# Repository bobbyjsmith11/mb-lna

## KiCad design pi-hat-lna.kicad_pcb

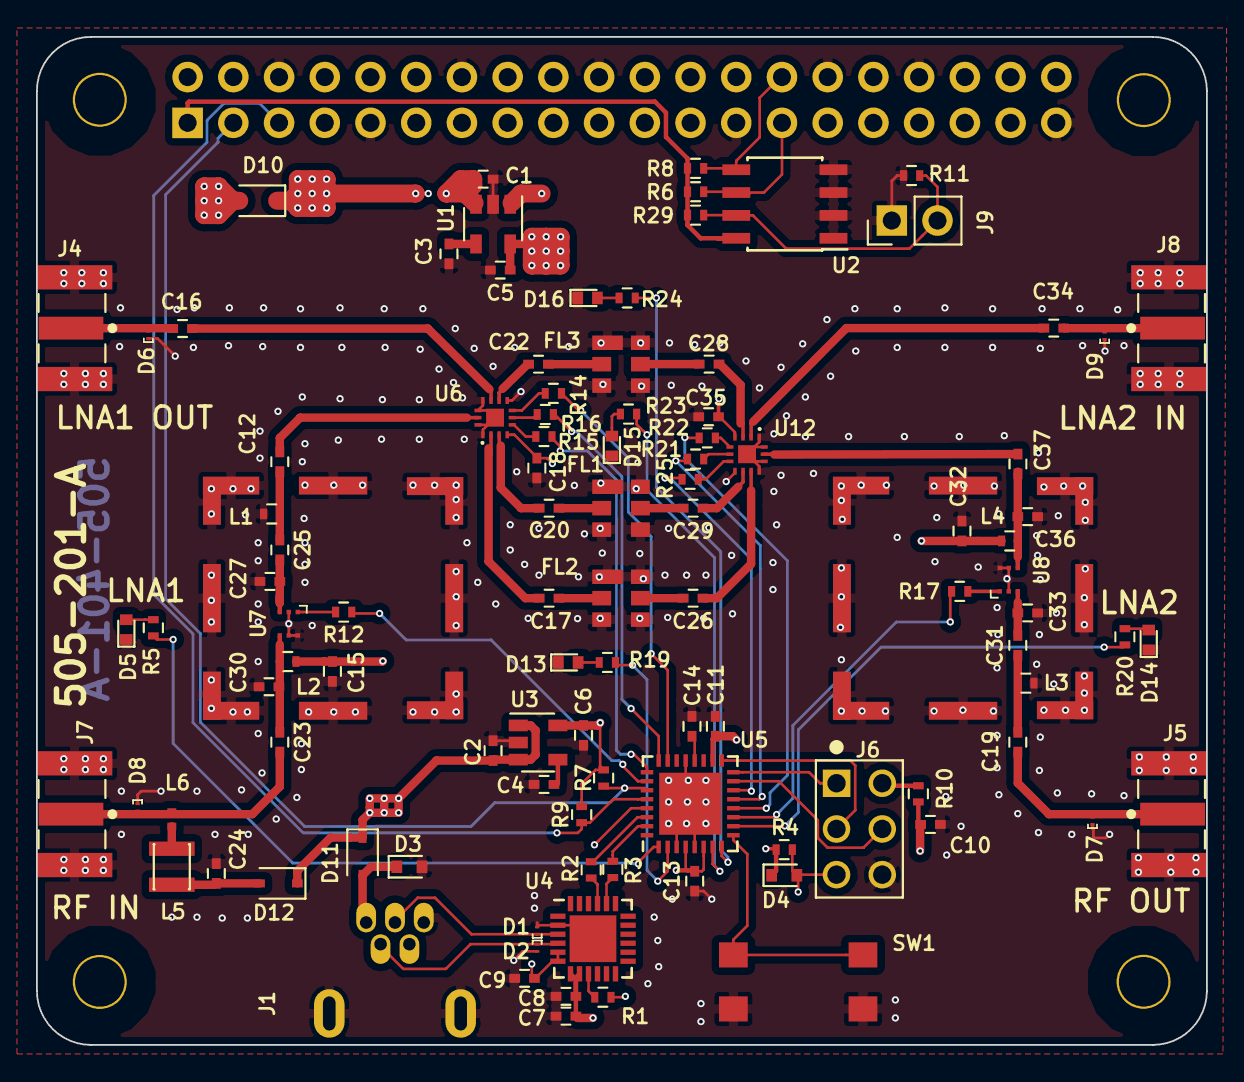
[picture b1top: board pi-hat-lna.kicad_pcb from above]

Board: 4 copper layers, 65.0 x 56.0 mm, 109 parts (1 on the bottom side), 83 nets.

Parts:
C1, C2, C5, C6, C7, C24: 1uF; C_0402
C3, C4, C8, C10, C11, C13, C14, C15, C18, C32, C35: 100nF; C_0402
C9: 4.7uF; C_0402
C12, C16, C17, C19, C20, C22, C23, C26, C28, C29, C34, C37: 100pF; C_0402
C25, C31: 30pF; C_0402
C27, C33: DNF; C_0402
C30, C36: 1pF; C_0402
D1, D2, D6, D7, D8, D9: ESD8472MUT5G; ONSEMI_0201_DSN2_153AF
D3, D4: PESD12VS1UB,115; D_SOD-523
D5, D13, D14, D15, D16: SML-LX0402SUGC-TR; LED_0402
D10, D11, D12: BAT165; D_SOD-323
FL1: SF2098E; SAW_3X3mm
FL2: SF2250E; SAW_3X3mm
FL3: SF2275E; SAW_3X3mm
H1, H2, H3, H4: 3mm_Mounting_Hole; NPTH_3mm_ID
J1: USB_B_Mini; USB_Mini-B_Molex-054819-0519
J3: DNF; PinSocket_2x20_P2.54mm_Vertical
J4, J5, J7, J8: SMA-J-P-H-ST-EM1
J6: 2x3 0.1" HEADER; FRAMATOME_67997-206HLF
J9: CONN_01X02; PinHeader_1x02_P2.54mm_Vertical
L1, L3: 22nH; L_0402
L2, L4: 39nH; L_0402
L5: 1uH; INDC2520X100
L6: BLM15AG121SN1D; FB_0402_NoSilk
M1, M2: DNF; 2118706-2
R1, R2, R5, R19, R20, R23, R24: 1K; R_0402
R3, R10: 0; R_0402
R4, R29: 10K; R_0402
R6, R7, R8, R9: 3.9K; R_0402
R11: DNF; R_0402
R12, R17: 1.4K; R_0402
R14, R15, R16, R21, R22, R25: 100; R_0402
SW1: TL3305AF160QG
U1, U3: TPS73233DBVR; SOT-23-5
U2: CAT24C32; SOIC-8_3.9x4.9mm_P1.27mm
U4: CP2102N-A01-GQFN24; QFN-24-1EP_4x4mm_Pitch0.5mm
U5: ATmega328P-MU; QFN-32-1EP_5x5mm_Pitch0.5mm
U6, U12: SKY13414-485LF; QFN45P200X200X55-15N
U7, U8: GRF4142; DFN1.5MMX1.5MMX0.45MM-6

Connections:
+3.3VA: C5.1, C15.2, C18.2, C32.2, C35.2, L2.1, L4.1, U1.5, U6.4, U12.4
+3V3: C6.1, C10.1, C11.1, C13.2, D4.1, R4.2, R7.2, R9.2, R10.2, U3.5, U5.4, U5.6, U5.18
+5V: C1.1, C2.1, D10.1, D11.1, D12.1, U1.1, U1.3, U3.1, U3.3
+5VP: C24.1, D12.2, L5.1
/ID_SC_EEPROM: J3.28, R8.2, U2.5
/ID_SD_EEPROM: J3.27, R6.2, U2.6
/P3V3_HAT: J3.1, R6.1, R8.1, R29.1, U2.8
/P5V_HAT: D10.2, J3.2, J3.4
/PI_SCL: J3.5, R9.1, U5.28
/PI_SDA: J3.3, R7.1, U5.27
/avr-usb/BTN: SW1.3, SW1.4, U5.9
/avr-usb/BYP_LNA1: R17.2, U5.11
/avr-usb/BYP_LNA2: R12.2, U5.26
/avr-usb/D_N: D2.1, J1.2, U4.4
/avr-usb/D_P: D1.1, J1.3, U4.3
/avr-usb/LED1: R5.2, U5.1
/avr-usb/LED2: R19.2, U5.2
/avr-usb/LED3: R20.2, U5.10
/avr-usb/LED4: R23.2, U5.7
/avr-usb/LED5: R24.2, U5.8
/avr-usb/MISO: J6.1, U5.16
/avr-usb/MOSI: J6.4, U5.15
/avr-usb/RXD_AT: R2.1, U5.30
/avr-usb/RXD_CP: R3.2, U4.20
/avr-usb/SCK: J6.3, U5.17
/avr-usb/SWA_V1: R14.1, U5.23
/avr-usb/SWA_V2: R16.1, U5.24
/avr-usb/SWA_V3: R15.1, U5.25
/avr-usb/SWB_V1: R25.1, U5.14
/avr-usb/SWB_V2: R21.1, U5.13
/avr-usb/SWB_V3: R22.1, U5.12
/avr-usb/TXD_AT: R3.1, U5.31
/avr-usb/TXD_CP: R2.2, U4.21
/avr-usb/VCC: J6.2, R10.1
/avr-usb/~RESET: D4.2, J6.5, R4.1, U5.29
GND: C1.2, C2.2, C3.2, C4.2, C5.2, C6.2, C7.2, C8.2, C9.1, C10.2, C11.2, C13.1, C14.2, C15.1, C18.1, C24.2, C27.2, C30.2, C32.1, C33.2, C35.1, C36.2, D1.2, D2.2, D3.2, D5.1, D6.1, D7.1, D8.1, D9.1, D13.1, D14.1, D15.1, D16.1, FL1.1, FL1.3, FL1.4, FL1.6, FL2.1, FL2.3, FL2.4, FL2.6, FL3.1, FL3.3, FL3.4, FL3.6, J1.5, J1.6, J3.6, J3.9, J3.14, J3.20, J3.25, J3.30, J3.34, J3.39, J4.2_1, J4.2_2, J4.3_1, J4.3_2, J5.2_1, J5.2_2, J5.3_1, J5.3_2, J6.6, J7.2_1, J7.2_2, J7.3_1, J7.3_2, J8.2_1, J8.2_2, J8.3_1, J8.3_2, J9.1, L1.2, L3.2, M1.1, M1.2, M1.3, M1.4, M1.5, M1.6, M1.7, M1.8, M2.1, M2.2, M2.3, M2.4, M2.5, M2.6, M2.7, M2.8, R11.1, SW1.1, SW1.2, U1.2, U2.1, U2.2, U2.3, U2.4, U3.2, U4.2, U4.25, U5.3, U5.5, U5.21, U5.33, U6.1, U6.8, U6.11, U6.12, U6.14, U6.15, U7.2, U7.5, U7.6, U8.2, U8.5, U8.6, U12.1, U12.8, U12.11, U12.12, U12.14, U12.15
unnamed: C3.1, U1.4
unnamed: C4.1, U3.4
unnamed: C9.2, R1.1, U4.5, U4.6
unnamed: C12.1, U6.13
unnamed: C12.2, C25.1, L1.1
unnamed: C14.1, U5.20
unnamed: C16.1, U6.10
unnamed: C16.2, D6.2, J4.1
unnamed: C17.1, U6.2
unnamed: C17.2, FL2.2
unnamed: C19.1, D7.2, J5.1
unnamed: C19.2, C31.1, L3.1
unnamed: C20.1, U6.3
unnamed: C20.2, FL1.2
unnamed: C22.1, U6.9
unnamed: C22.2, FL3.2
unnamed: C23.1, C30.1, L2.2, U7.4
unnamed: C23.2, D8.2, J7.1, L6.2
unnamed: C25.2, C27.1, U7.3
unnamed: C26.1, U12.10
unnamed: C26.2, FL2.5
unnamed: C28.1, U12.3
unnamed: C28.2, FL3.5
unnamed: C29.1, U12.9
unnamed: C29.2, FL1.5
unnamed: C31.2, C33.1, U8.3
unnamed: C34.1, U12.2
unnamed: C34.2, D9.2, J8.1
unnamed: C36.1, C37.1, L4.2, U8.4
unnamed: C37.2, U12.13
unnamed: D5.2, R5.1
unnamed: D13.2, R19.1
unnamed: D14.2, R20.1
unnamed: D15.2, R23.1
unnamed: D16.2, R24.1
unnamed: J9.2, R11.2, R29.2, U2.7
unnamed: L5.2, L6.1
unnamed: R1.2, U4.9
unnamed: R12.1, U7.1
unnamed: R14.2, U6.7
unnamed: R15.2, U6.5
unnamed: R16.2, U6.6
unnamed: R17.1, U8.1
unnamed: R21.2, U12.6
unnamed: R22.2, U12.5
unnamed: R25.2, U12.7
VBUS: C7.1, C8.1, D3.1, D11.2, J1.1, U4.7, U4.8

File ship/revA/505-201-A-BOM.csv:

Component,Description,References,Value,Quantity Per PCB,Part Number,Notes,Manufacturer
1,CAP CER 0.1UF 10V X5R 0402,C3 C4 C8 C10 C11 C13 C14 C15 C18 C32 C35,100nF,11,CL05A104MP5NNNC,6.3V or greater,Samsung
2,CAP CER 100PF 25V C0G/NP0 01005,C12 C16 C17 C19 C20 C22 C23 C26 C28 C29 C34 C37,100pF,12,GRM0225C1E101GA02L,,Murata
3,CAP CER 1PF 50V C0G/NP0 0402,C30 C36,1pF,2,GJM1555C1H1R0BB01D,,Murata
4,CAP 1UF 6.3V X5R 0402,C1 C2 C5 C6 C7 C24,1uF,6,GRM153R60J105ME95D,6.3V or greater,Murata
5,CAP CER 30PF 50V C0G/NP0 0402,C25 C31,30pF,2,GJM1555C1H300JB01D,,Murata
6,CAP CER 4.7UF 10V X5R 0402,C9,4.7uF,1,C1005X5R1A475M050BC,6.3V or greater,TDK
7,Diode Schottky 40V 750mA (DC) Surface Mount PG-SOD323-2,D10 D11 D12,BAT165,3,BAT165E6327HTSA1,,Infineon
8,TVS DIODE 5.3V 14V 2X3DFN,D1 D2 D6 D7 D8 D9,ESD8472MUT5G,6,ESD8472MUT5G,,ON Semiconductor
9,TVS DIODE 12V 35V SOD523,D3 D4,"PESD12VS1UB,115",2,"PESD12VS1UB,115",,Nexperia
10,LED GREEN CLEAR SMD,D5 D13 D14 D15 D16,SML-LX0402SUGC-TR,5,SML-LX0402SUGC-TR,,Lumex
11,FILTER SAW 915MHZ 6SMD,FL1,SF2098E,1,SF2098E,,Murata
12,FILTER SAW FC=1615MHZ BW=20MHz 6SMD,FL2,SF2250E,1,SF2250E,,Murata
13,FILTER SAW FC=1542.5MHZ BW=35MHz,FL3,SF2275E,1,SF2275E,,Murata
14,"Connector Header Through Hole 6 position 0.100"" (2.54mm)",J6,"2x3 0.1"" HEADER",1,67997-206HLF,,Amphenol
15,CONN HEADER 2POS VERT T/H,J9,CONN_01X02,1,77311-118-02LF,,Amphenol
16,"SMA Connector Jack, Female Socket 50 Ohm Board Edge, End Launch Solder",J4 J5 J7 J8,SMA-J-P-H-ST-EM1,4,SMA-J-P-H-ST-EM1,,Samtec
17,"USB - mini B USB 2.0 OTG Receptacle Connector 5 Position Through Hole, Right Angle",J1,USB_B_Mini,1,0548190519,,Molex
18,1µH Unshielded Wirewound Inductor 370mA 1.75 Ohm Max 1008 (2520 Metric),L5,1uH,1,LQW2UAS1R0J00L,,Murata
19,FIXED IND 22NH 350MA 420 MOHM,L1 L3,22nH,2,LQG15HS22NJ02D,,Murata
20,FIXED IND 39NH 300MA 650 MOHM,L2 L4,39nH,2,LQG15HS39NJ02D,,Murata
21,FERRITE BEAD 120 OHM 0402 1LN,L6,BLM15AG121SN1D,1,BLM15AG121SN1D,,Murata
22,RES SMD 0 OHM JUMPER 1/10W 0402,R3 R10,0,2,ERJ-2GE0R00X,any 0402 jumper,Panasonic
23,RES SMD 1.4K OHM 1% 1/10W 0402,R12 R17,1.4K,2,ERJ-2RKF1401X,,Panasonic
24,RES SMD 1K OHM 1% 1/10W 0402,R14 R15 R16 R21 R22 R25,100,6,ERJ-2RKF1001X,,Panasonic
25,RES SMD 10K OHM 1% 1/10W 0402,R4 R29,10K,2,ERJ-2RKF1002X,,Panasonic
26,RES SMD 1K OHM 1% 1/10W 0402,R1 R2 R5 R19 R20 R23 R24,1K,7,ERJ-2RKF1001X,,Panasonic
27,RES SMD 3.9K OHM 1% 1/10W 0402,R6 R7 R8 R9,3.9K,4,RC0402FR-073K9L,,Panasonic
28,Tactile Switch SPST-NO Top Actuated Surface Mount,SW1,TL3305AF160QG,1,TL3305AF160QG,,E-Switch
29,IC MCU 8BIT 32KB FLASH 32VQFN,U5,ATmega328P-MU,1,ATMEGA328P-MUR,,Microchip Technology
30,IC EEPROM 32K I2C 1MHZ 8SOIC,U2,CAT24C32,1,CAT24C32WI-GT3,,ON Semiconductor
31,IC BRIDGE USB TO UART 24QFN,U4,CP2102N-A01-GQFN24,1,CP2102N-A01-GQFN24,,Silicon Labs
32,RF Amplifier .1-3.8GHz GaAs Gain 16dB,U7 U8,GRF4142,2,GRF4142,,Guerilla RF
33,RF Switch IC SP4T 3GHz 50 Ohm 14-QFN (2x2),U6 U12,SKY13414-485LF,2,SKY13414-485LF,,Skyworks
34,IC REG LINEAR 3.3V 250MA SOT23-5,U1 U3,TPS73233DBVR,2,TPS73233DBVR,,Texas Instruments





Component Groups:,38
Component Count:,105
Fitted Components:,99
Number of PCBs:,1
Total components:,99
Schematic Version:,A
Schematic Date:,
BoM Date:,Tue 23 Oct 2018 06:03:50 AM CDT
Schematic Source:,/home/bsmith/kicad/projects/mb-lna/pi-hat-lna.sch
KiCad Version:,Eeschema 5.0.0-fee4fd1~66~ubuntu16.04.1

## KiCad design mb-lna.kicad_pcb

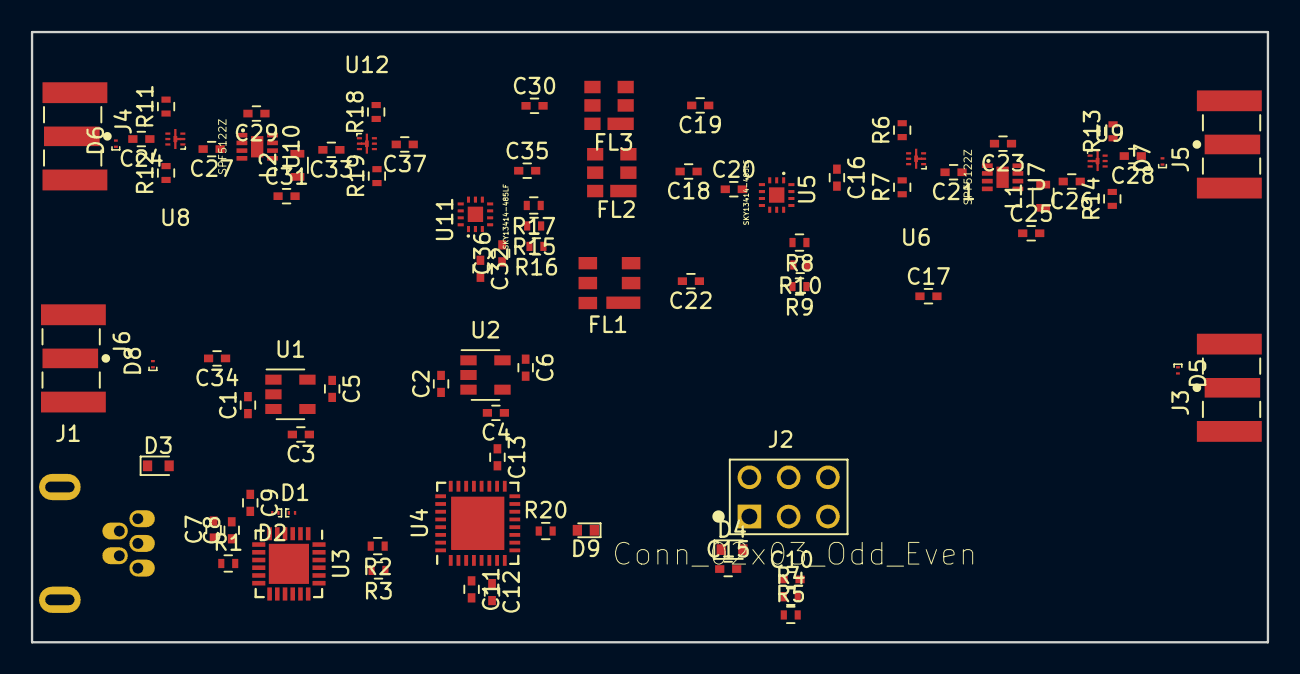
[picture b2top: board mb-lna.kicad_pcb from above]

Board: 2 copper layers, 80.0 x 39.5 mm, 88 parts (0 on the bottom side), 82 nets, no tracks yet.

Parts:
C1, C2, C5, C6, C7: 1uF; C_0402
C3, C4, C8, C10, C11, C12, C13, C15, C20, C25, C31, C36: 100nF; C_0402
C9: 4.7uF; C_0402
C16, C17, C18, C19, C21, C22, C23, C24, C26, C27, C28, C29, C30, C32, C33, C34, C35, C37: 100pF; C_0402
D1, D2, D5, D6, D7, D8: ESD8472MUT5G; ONSEMI_0201_DSN2_153AF
D3, D4: PESD12VS1UB,115; D_SOD-523
D9: SML-LX0402SUGC-TR; LED_0402
FL1: TA1090EC; SAW_3.8X3.8MM
FL2: SF2098E; SAW_3X3mm
FL3: SF2250E; SAW_3X3mm
J1: USB_B_Mini; USB_Mini-B_Molex-054819-0519
J2: Conn_02x03_Odd_Even; FRAMATOME_67997-206HLF
J3, J4, J5, J6: SMA-J-P-H-ST-EM1
L1, L2: 150nH; L_0603
R1, R2, R20: 1K; R_0402
R3, R5: 0; R_0402
R4: 10K; R_0402
R6, R7, R8, R9, R10, R11, R12, R13, R14, R15, R16, R17, R18, R19: 100; R_0402
U1, U2: TPS73233DBVR; SOT-23-5
U3: CP2102N-A01-GQFN24; QFN-24-1EP_4x4mm_Pitch0.5mm
U4: ATmega328P-MU; QFN-32-1EP_5x5mm_Pitch0.5mm
U5, U11: SKY13414-485LF; QFN45P200X200X55-15N
U6, U8, U9, U12: SKY13351-378LF; SKY_QFN6_1x1mm
U7, U10: SPF5122Z; DFN-8

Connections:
+3.3VA: C5.1, C20.2, C25.2, C31.2, C36.2, L1.1, L2.1, U1.5, U5.4, U11.4
+3V3: C6.1, C10.1, C11.1, C12.1, C13.2, D4.1, R4.2, R5.2, U2.5, U4.4, U4.6, U4.18
/rf_section/BYP_LNA1: R11.2, R18.2, U4.23
/rf_section/BYP_LNA1_N: R12.1, R19.1, U4.24
/rf_section/BYP_LNA2: R6.2, R13.2, U4.25
/rf_section/BYP_LNA2_N: R7.1, R14.1, U4.26
/rf_section/SWA_V1: R8.1, U4.32
/rf_section/SWA_V2: R10.1, U4.1
/rf_section/SWA_V3: R9.1, U4.2
/rf_section/SWB_V1: R17.1, U4.9
/rf_section/SWB_V2: R15.1, U4.10
/rf_section/SWB_V3: R16.1, U4.11
/usb-micro/D_N: D2.1, J1.2, U3.4
/usb-micro/D_P: D1.1, J1.3, U3.3
/usb-micro/LED_GRN: R20.1, U4.12
/usb-micro/MISO: J2.1, U4.16
/usb-micro/MOSI: J2.4, U4.15
/usb-micro/RXD_AT: R2.1, U4.30
/usb-micro/RXD_CP: R3.2, U3.20
/usb-micro/SCK: J2.3, U4.17
/usb-micro/TXD_AT: R3.1, U4.31
/usb-micro/TXD_CP: R2.2, U3.21
/usb-micro/VCC: J2.2, R5.1
/usb-micro/~RESET: D4.2, J2.5, R4.1, U4.29
GND: C1.2, C2.2, C3.2, C4.2, C5.2, C6.2, C7.2, C8.2, C9.1, C10.2, C11.2, C12.2, C13.1, C15.2, C20.1, C25.1, C31.1, C36.1, D1.2, D2.2, D3.2, D5.1, D6.1, D7.1, D8.1, D9.1, FL1.1, FL1.3, FL1.4, FL1.6, FL2.1, FL2.3, FL2.4, FL2.6, FL3.1, FL3.3, FL3.4, FL3.6, J1.5, J1.6, J2.6, J3.2_1, J3.2_2, J3.3_1, J3.3_2, J4.2_1, J4.2_2, J4.3_1, J4.3_2, J5.2_1, J5.2_2, J5.3_1, J5.3_2, J6.2_1, J6.2_2, J6.3_1, J6.3_2, U1.2, U2.2, U3.2, U3.25, U4.3, U4.5, U4.21, U4.33, U5.1, U5.8, U5.11, U5.12, U5.14, U5.15, U6.2, U7.1, U7.4, U7.5, U7.8, U7.9, U8.2, U9.2, U10.1, U10.4, U10.5, U10.8, U10.9, U11.1, U11.8, U11.11, U11.12, U11.14, U11.15, U12.2
unnamed: C3.1, U1.4
unnamed: C4.1, U2.4
unnamed: C9.2, R1.1, U3.5, U3.6
unnamed: C15.1, U4.20
unnamed: C16.1, U6.5
unnamed: C16.2, U5.13
unnamed: C17.1, U5.10
unnamed: C17.2, D5.2, J3.1
unnamed: C18.1, U5.2
unnamed: C18.2, FL2.2
unnamed: C19.1, U5.3
unnamed: C19.2, FL3.2
unnamed: C21.1, U7.2, U7.3
unnamed: C21.2, U6.1
unnamed: C22.1, U5.9
unnamed: C22.2, FL1.2
unnamed: C23.1, U9.1
unnamed: C23.2, U6.3
unnamed: C24.1, U8.5
unnamed: C24.2, D6.2, J4.1
unnamed: C26.1, U9.3
unnamed: C26.2, L1.2, U7.6, U7.7
unnamed: C27.1, U10.2, U10.3
unnamed: C27.2, U8.1
unnamed: C28.1, D7.2, J5.1
unnamed: C28.2, U9.5
unnamed: C29.1, U12.1
unnamed: C29.2, U8.3
unnamed: C30.1, U11.10
unnamed: C30.2, FL3.5
unnamed: C32.1, U11.3
unnamed: C32.2, FL1.5
unnamed: C33.1, U12.3
unnamed: C33.2, L2.2, U10.6, U10.7
unnamed: C34.1, U11.2
unnamed: C34.2, D8.2, J6.1
unnamed: C35.1, U11.9
unnamed: C35.2, FL2.5
unnamed: C37.1, U11.13
unnamed: C37.2, U12.5
unnamed: D9.2, R20.2
unnamed: R1.2, U3.9
unnamed: R6.1, U6.4
unnamed: R7.2, U6.6
unnamed: R8.2, U5.7
unnamed: R9.2, U5.5
unnamed: R10.2, U5.6
unnamed: R11.1, U8.4
unnamed: R12.2, U8.6
unnamed: R13.1, U9.6
unnamed: R14.2, U9.4
unnamed: R15.2, U11.6
unnamed: R16.2, U11.5
unnamed: R17.2, U11.7
unnamed: R18.1, U12.6
unnamed: R19.2, U12.4
VBUS: C1.1, C2.1, C7.1, C8.1, D3.1, J1.1, U1.1, U1.3, U2.1, U2.3, U3.7, U3.8

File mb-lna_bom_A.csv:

Component,Description,Part,References,Value,Footprint,Quantity Per PCB,Datasheet,Part Number,Package,Alternate Part Number,Notes,Manufacturer,Field8,Field4,Field7,Field6,Field5
1,CAP CER 0.1UF 10V X5R 0402,C,C3 C4 C8 C10 C11 C12 C13 C14 C15 C20 C25 C31 C36,100nF,C_0402,13,~,CL05A104MP5NNNC,0402,GRM022R60J104ME15L,6.3V or greater,,,,,,
2,CAP CER 100PF 25V C0G/NP0 01005,C,C16 C17 C18 C19 C21 C22 C23 C24 C26 C27 C28 C29 C30 C32 C33 C34 C35 C37,100pF,C_0402,18,~,GRM0225C1E101GA02L,0402,500X07N101MV4T,,Murata,,,,,
3,CAP 1UF 6.3V X5R 0402,C,C1 C2 C5 C6 C7,1uF,C_0402,5,~,GRM153R60J105ME95D,0402,CL05A105MQ3LNNH,6.3V or greater,Murata,,,,,
4,CAP CER 4.7UF 10V X5R 0402,C,C9,4.7uF,C_0402,1,~,C1005X5R1A475M050BC,0402,0402ZD475MAT2A,6.3V or greater,TDK,,,,,
5,TVS DIODE 5.3V 14V 2X3DFN,TVS-2-pin,D1 D2 D5 D6 D7 D8,ESD8472MUT5G,ONSEMI_0201_DSN2_153AF,6,http://www.onsemi.com/pub/Collateral/ESD8472-D.PDF,ESD8472MUT5G,0201 (0603 Metric),,,ON Semiconductor,,,,,
6,TVS DIODE 12V 35V SOD523,1.5KExxA,D3 D4,"PESD12VS1UB,115",D_SOD-523,2,https://assets.nexperia.com/documents/data-sheet/PESDXS1UB_S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,"PESD12VS1UB,115",SOD-523,,,Nexperia,,,,,
7,LED GREEN CLEAR SMD,LED,D9,SML-LX0402SUGC-TR,LED_0402,1,https://www.lumex.com/content/files/ProductAttachment/SML-LX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,SML-LX0402SUGC-TR,0402,,,Lumex,,,,,
8,FILTER SAW 915MHZ 6SMD,SAW_3X3mm,FL2,SF2098E,SAW_3X3mm,1,https://wireless.murata.com/RFM/data/sf2098e.pdf,SF2098E,SAW 3x3mm,,,Murata,,,,,
9,FILTER SAW 1.615GHZ 6SMD,SAW_3X3mm,FL3,SF2250E,SAW_3X3mm,1,https://wireless.murata.com/RFM/data/sf2250e.pdf,SF2250E,SAW 3x3mm,,,Murata,,,,,
10,FILTER SAW 1090MHz,SAW_3X3mm,FL1,TA1090EC,SAW_3.8X3.8MM,1,https://www.rfmw.com/datasheets/tai-saw/TA1090EC%20_Rev.3.0_.pdf,TA1090EC,SAW 3.8x3.8mm,,,TAI-SAW,,,,,
11,"Connector Header Through Hole 6 position 0.100"" (2.54mm)",Conn_02x03_Odd_Even,J2,Conn_02x03_Odd_Even,FRAMATOME_67997-206HLF,1,https://cdn.amphenol-icc.com/media/wysiwyg/files/drawing/67996.pdf,67997-206HLF,,M20-9980345,,Amphenol,,,,,
12,"SMA Connector Jack, Female Socket 50 Ohm Board Edge, End Launch Solder",SMA-J-P-H-ST-EM1,J3 J4 J5 J6,SMA-J-P-H-ST-EM1,SMA-J-P-H-ST-EM1,4,Connector SMA F 50Ohm Solder ST Edge Mount Gold Over Nickel Tray,SMA-J-P-H-ST-EM1,,,,Samtec,Samtec,None,2.95 USD,Good,SMA-J-P-H-ST-EM1
13,"USB - mini B USB 2.0 OTG Receptacle Connector 5 Position Through Hole, Right Angle",USB_B_Mini,J1,USB_B_Mini,USB_Mini-B_Molex-054819-0519,1,https://www.molex.com/pdm_docs/sd/548190519_sd.pdf,0548190519,,,,Molex,,,,,
14,FIXED IND 150NH 300MA 1.4 OHM,L,L1 L2,150nH,L_0603,2,~,L-14CR15JV4T,0603,HK1608R15J-T,,Johanson Technology,,,,,
15,RES SMD 0 OHM JUMPER 1/10W 0402,R,R3 R5,0,R_0402,2,~,ERJ-2GE0R00X,0402,RC1005J000CS,any 0402 jumper,Panasonic,,,,,
16,RES SMD 1K OHM 1% 1/10W 0402,R,R6 R7 R8 R9 R10 R11 R12 R13 R14 R15 R16 R17 R18 R19,100,R_0402,14,~,ERJ-2RKF1001X,0402,RT0402FRE071KL,,Panasonic,,,,,
17,RES SMD 10K OHM 1% 1/10W 0402,R,R4,10K,R_0402,1,~,ERJ-2RKF1002X,0402,RMCF0402FT10K0,,Panasonic,,,,,
18,RES SMD 1K OHM 1% 1/10W 0402,R,R1 R2 R20,1K,R_0402,3,~,ERJ-2RKF1001X,0402,RCA04021K00FKEDHP,,Panasonic,,,,,
19,IC MCU 8BIT 32KB FLASH 32VQFN,ATmega328P-MU,U4,ATmega328P-MU,QFN-32-1EP_5x5mm_P0.5mm_EP3.1x3.1mm,1,http://ww1.microchip.com/downloads/en/DeviceDoc/ATmega328_P%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,ATMEGA328P-MUR,32-VFQFN,,,Microchip Technology,,,,,
20,IC BRIDGE USB TO UART 24QFN,CP2102N-A01-GQFN24,U3,CP2102N-A01-GQFN24,QFN-24-1EP_4x4mm_P0.5mm_EP2.6x2.6mm,1,http://www.silabs.com/support%20documents/technicaldocs/cp21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,CP2102N-A01-GQFN24,24-VFQFN,,,Silicon Labs,,,,,
21,IC SW SPDT 2.0-6GHZ GAAS 6MLPD,SKY13351-378LF,U6 U8 U9 U12,SKY13351-378LF,SKY_QFN6_1x1mm,4,http://www.skyworksinc.com/uploads/documents/SKY13351_378LF_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,SKY13351-378LF,6MLPD,,,Skyworks,,,,,
22,RF Switch IC SP4T 3GHz 50 Ohm 14-QFN (2x2),SKY13414-485LF,U5 U11,SKY13414-485LF,QFN45P200X200X55-15N,2,http://www.skyworksinc.com/uploads/documents/SKY13414_485LF_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,SKY13414-485LF,14-QFN,,,Skyworks,,,,,
23,RF Amplifier .05-4GHz SSG 12.2dB NF .65dB GaAs,SPF5122Z,U7 U10,SPF5122Z,DFN-8,2,https://www.mouser.com/datasheet/2/412/pf5122z_data_sheet-78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,SPF5122Z,DFN8,,,Qorvo,,,,,
24,IC REG LINEAR 3.3V 250MA SOT23-5,ADP7142AUZJ,U1 U2,TPS73233DBVR,TSOT-23-5,2,http://www.ti.com/lit/ds/symlink/tps732.pdf,TPS73233DBVR,SOT-23-5,ADP7142AUJZ-3.3-R7,,Texas Instruments,,,,,





Component Groups:,24
Component Count:,89
Fitted Components:,89
Number of PCBs:,1
Total components:,89
Schematic Version:,A
Schematic Date:,2018-08-18
BoM Date:,Mon 20 Aug 2018 05:22:57 AM CDT
Schematic Source:,/home/bsmith/kicad/projects/mb-lna/mb-lna.sch
KiCad Version:,Eeschema 5.0.0-fee4fd1~66~ubuntu16.04.1

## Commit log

2018-08-19 Need yet to add the AVR programming connector and the RF filters
2018-08-19 Schematic complete. Ready for review.
2018-08-19 More updates. Added LED to AVR to help with bring up and debug.
2018-08-21 Started parts placement and fixed some RF routing to accomodate layout
2018-08-23 added the netlist and BOM
2018-08-23 Added 3D model for usb mini connector
2018-08-25 Changed design to be a pi-hat
2018-08-26 Almost all 3D models have been added. Rough parts placement complete.
2018-08-27 Added 3D models to project library
2018-09-03 Trimmed unnecessary parts from the Pi power circuitry. Now the Pi 5V is diode or'd with VBUS from the USB
2018-09-09 Can now power via: 1. USB 2. R-Pi 3. Bias TEE
2018-10-11 Finally have the stackup
2018-10-14 I think the layout is ready for review
2018-10-19 Cleaned up BOM and added part numbers to the layout.
2018-10-19 Cleaned up all vias and tracks. FYI - always work in mils!!!
2018-10-20 Board is out for quote to several places.
2018-10-21 The project footprints have been locally archived now. Now, all of the footprints are loacl within the project.
2018-10-22 Changed the 50 Ohm traces from 18.5 mils to 16 mils in order to accomodate one of the standard 4 layer stackups available from PCBWay.
2018-10-23 More dicking around with CMs
2018-10-24 Updated the I2C lines from the R-pi to connect to the appropriate pins on the ATMEGA328P: SDA - pin 27 (PC4) SCL - pin 28 (PC5) Also, updated the layout accordingly.
2018-10-24 PCBWay has agreed to do the stackup called out on the drawing. I've updated the schematic and layout accounting for the I2C changes related to the AtMega328P
2018-11-04 fixed the board outline so that step files can be exported
